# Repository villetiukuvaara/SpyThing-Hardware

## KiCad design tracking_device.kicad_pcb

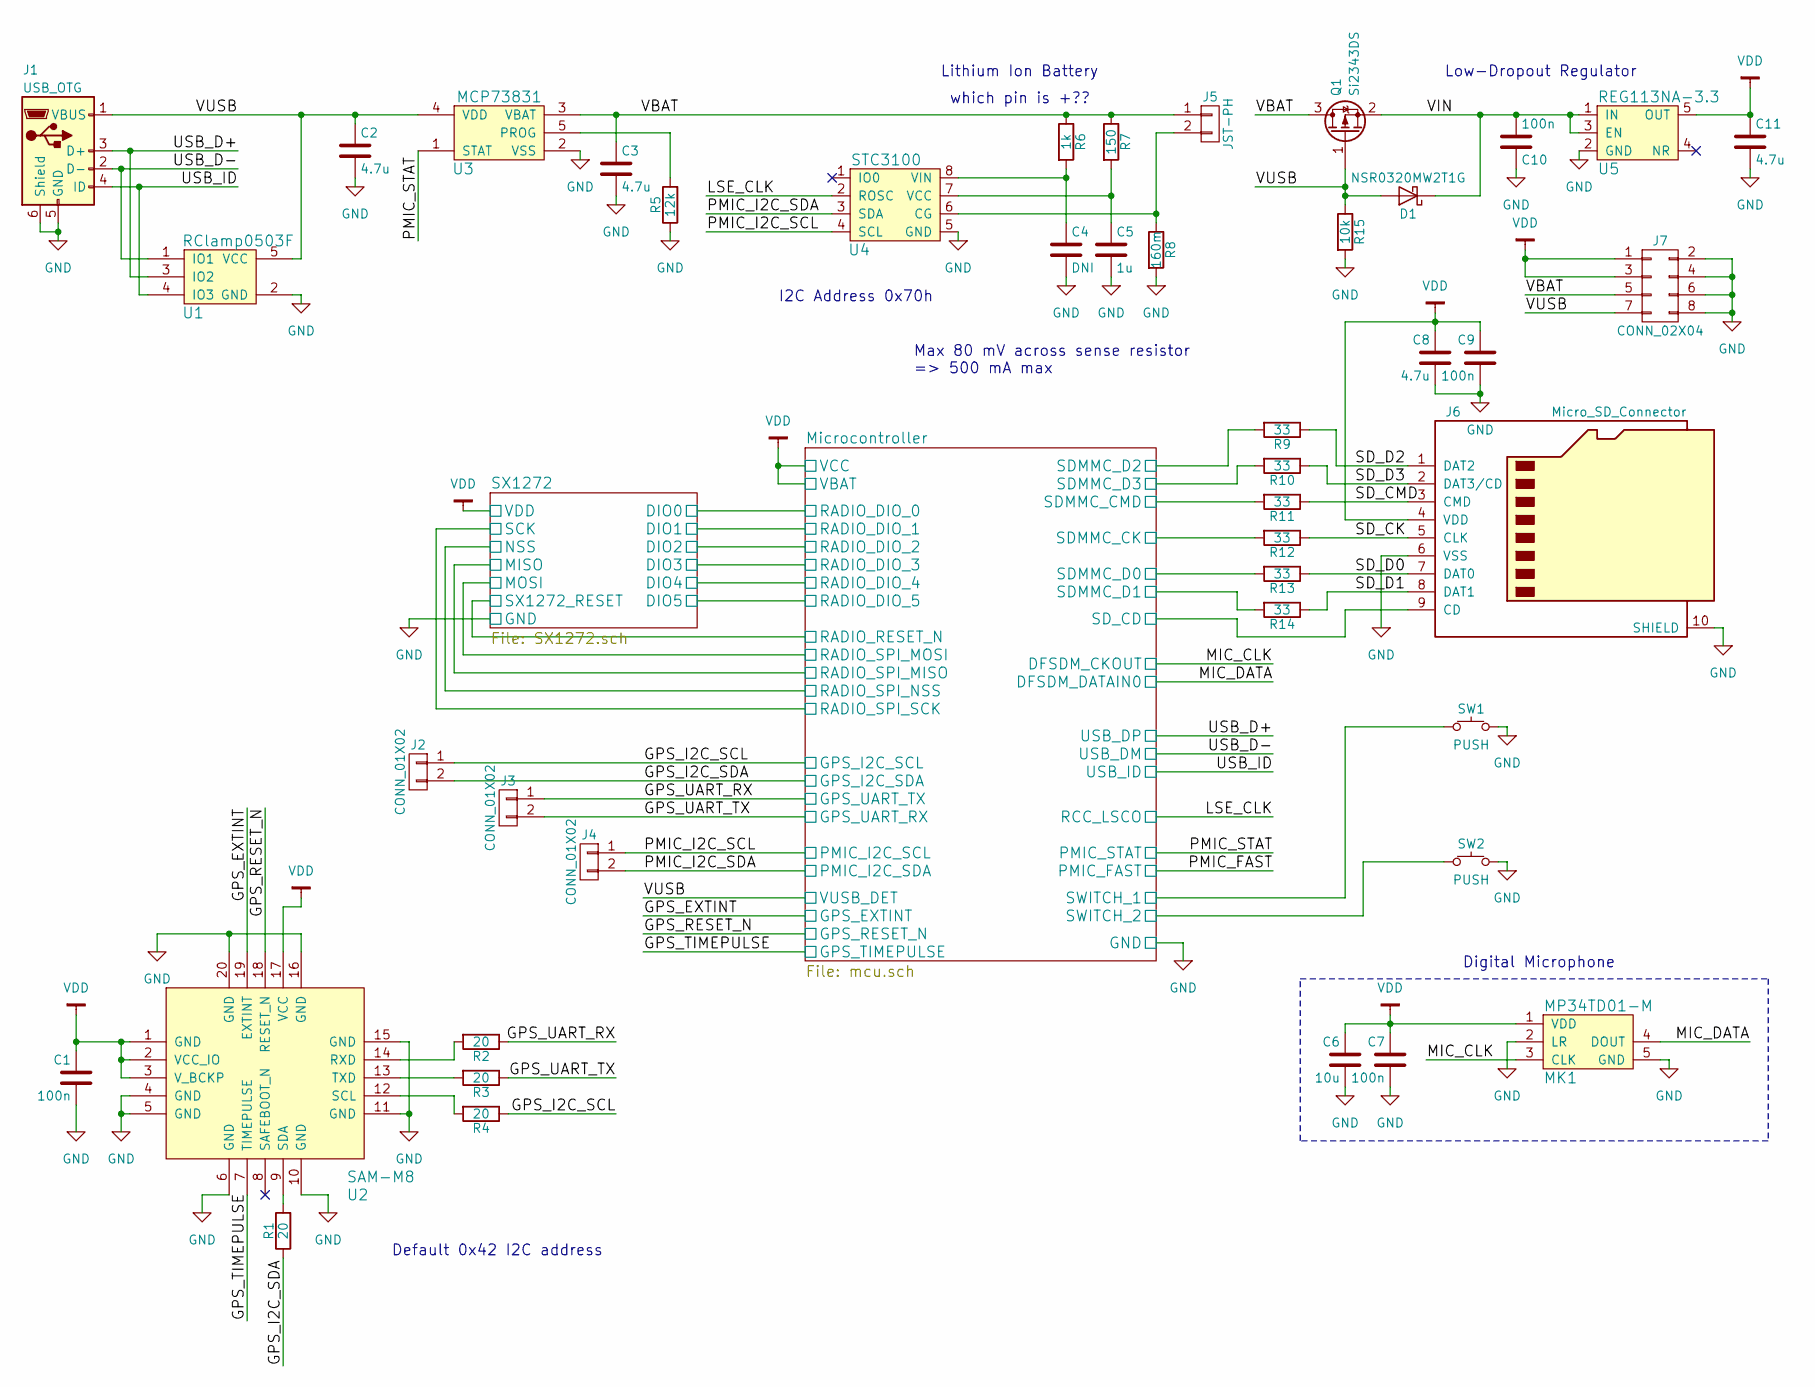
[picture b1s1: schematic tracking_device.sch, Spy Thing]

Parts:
C1, C7, C9, C10: 100n; C_0805_HandSoldering
C2, C3, C8, C11: 4.7u; C_0805_HandSoldering
C4: DNI; C_0805_HandSoldering
C5: 1u; C_0805_HandSoldering
C6: 10u; C_0805_HandSoldering
D1: NSR0320MW2T1G; D_SOD-323_HandSoldering
J1: USB_OTG; FCI_10118192-0001LF
J2, J3, J4: CONN_01X02; Pin_Header_Straight_2x01_Pitch2.54mm
J5: JST-PH; PH-2AWD
J6: Micro_SD_Connector; SD_Card_Connector_Ebay
J7: CONN_02X04; HEADER_M_2.54MM_2R8P_ST_AU_PTH
MK1: MP34TD01-M; MIC_3x4
Q1: Si2343DS; SOT-23_Handsoldering
R1, R2, R3, R4: 20; R_0805_HandSoldering
R5: 12k; R_0805_HandSoldering
R6: 1k; R_0805_HandSoldering
R7: 150; R_0805_HandSoldering
R8: 160m; R_0805_HandSoldering
R9, R10, R11, R12, R13, R14: 33; R_0805_HandSoldering
R15: 10k; R_0805_HandSoldering
SW1, SW2: PUSH; SW_3.1x3.1
U1: RClamp0503F; SOT-353_SC-70-5_Handsoldering
U2: SAM-M8
U3: MCP73831; SOT-23-5
U4: STC3100; DFN-8-1EP_3x3mm_Pitch0.5mm
U5: REG113NA-3.3; SOT-23-5_HandSoldering

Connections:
/GPS_EXTINT: U2.19 (EXTINT); also elsewhere on the board
/GPS_I2C_SCL: J2.1, R4.1; also elsewhere on the board
/GPS_I2C_SDA: J2.2, R1.1; also elsewhere on the board
/GPS_RESET_N: U2.18 (RESET_N); also elsewhere on the board
/GPS_TIMEPULSE: U2.7 (TIMEPULSE); also elsewhere on the board
/GPS_UART_RX: J3.1, R2.1; also elsewhere on the board
/GPS_UART_TX: J3.2, R3.1; also elsewhere on the board
/LSE_CLK: U4.2 (ROSC); also elsewhere on the board
/MIC_CLK: MK1.3 (CLK); also elsewhere on the board
/MIC_DATA: MK1.4 (DOUT); also elsewhere on the board
/Microcontroller/SDMMC_CK: R12.2; also elsewhere on the board
/Microcontroller/SDMMC_CMD: R11.2; also elsewhere on the board
/Microcontroller/SDMMC_D0: R13.2; also elsewhere on the board
/Microcontroller/SDMMC_D1: R14.2; also elsewhere on the board
/Microcontroller/SDMMC_D2: R9.2; also elsewhere on the board
/Microcontroller/SDMMC_D3: R10.2; also elsewhere on the board
/Microcontroller/SD_CD: J6.9 (CD); also elsewhere on the board
/Microcontroller/SWITCH_1: SW1.1; also elsewhere on the board
/Microcontroller/SWITCH_2: SW2.1; also elsewhere on the board
/PMIC_I2C_SCL: J4.1, U4.4 (SCL); also elsewhere on the board
/PMIC_I2C_SDA: J4.2, U4.3 (SDA); also elsewhere on the board
/PMIC_STAT: U3.1 (STAT); also elsewhere on the board
/SD_CK: J6.5 (CLK), R12.1
/SD_CMD: J6.3 (CMD), R11.1
/SD_D0: J6.7 (DAT0), R13.1
/SD_D1: J6.8 (DAT1), R14.1
/SD_D2: J6.1 (DAT2), R9.1
/SD_D3: J6.2 (DAT3/CD), R10.1
/USB_D+: J1.3 (D+), U1.3 (IO2); also elsewhere on the board
/USB_D-: J1.2 (D-), U1.1 (IO1); also elsewhere on the board
/USB_ID: J1.4 (ID), U1.4 (IO3); also elsewhere on the board
/VBAT: C3.1, J5.1, J7.5, Q1.3 (D), R6.1, R7.1, U3.3 (VBAT)
/VIN: C10.2, D1.1 (K), Q1.2 (S), U5.1 (IN), U5.3 (EN)
/VUSB: C2.1, D1.2 (A), J1.1 (VBUS), J7.7, Q1.1 (G), R15.1, U1.5 (VCC), U3.4 (VDD); also elsewhere on the board
GND: C1.2, C2.2, C3.2, C4.2, C5.2, C6.2, C7.2, C8.2, C9.2, C10.1, C11.2, J1.5 (GND), J1.6 (Shield), J6.6 (VSS), J6.10 (SHIELD), J7.2, J7.4, J7.6, J7.8, MK1.2 (LR), MK1.5 (GND), R5.1, R8.2, R15.2, SW1.2, SW2.2, U1.2 (GND), U2.4 (GND), U2.5 (GND), U2.6 (GND), U2.10 (GND), U2.11 (GND), U2.15 (GND), U2.16 (GND), U2.20 (GND), U3.2 (VSS), U4.5 (GND), U5.2 (GND); also elsewhere on the board
unnamed: C4.1, R6.2, U4.8 (VIN)
unnamed: C5.1, R7.2, U4.7 (VCC)
unnamed: J5.2, R8.1, U4.6 (CG)
unnamed: R1.2, U2.9 (SDA)
unnamed: R2.2, U2.14 (RXD)
unnamed: R3.2, U2.13 (TXD)
unnamed: R4.2, U2.12 (SCL)
unnamed: R5.2, U3.5 (PROG)
VDD: C1.1, C6.1, C7.1, C8.1, C9.1, C11.1, J6.4 (VDD), J7.1, J7.3, MK1.1 (VDD), U2.1 (GND), U2.2 (VCC_IO), U2.3 (V_BCKP), U2.17 (VCC), U5.5 (OUT); also elsewhere on the board

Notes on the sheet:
Lithium Ion Battery
Low-Dropout Regulator
Max 80 mV across sense resistor => 500 mA max
Digital Microphone
I2C Address 0x70h
Default 0x42 I2C address
which pin is +??

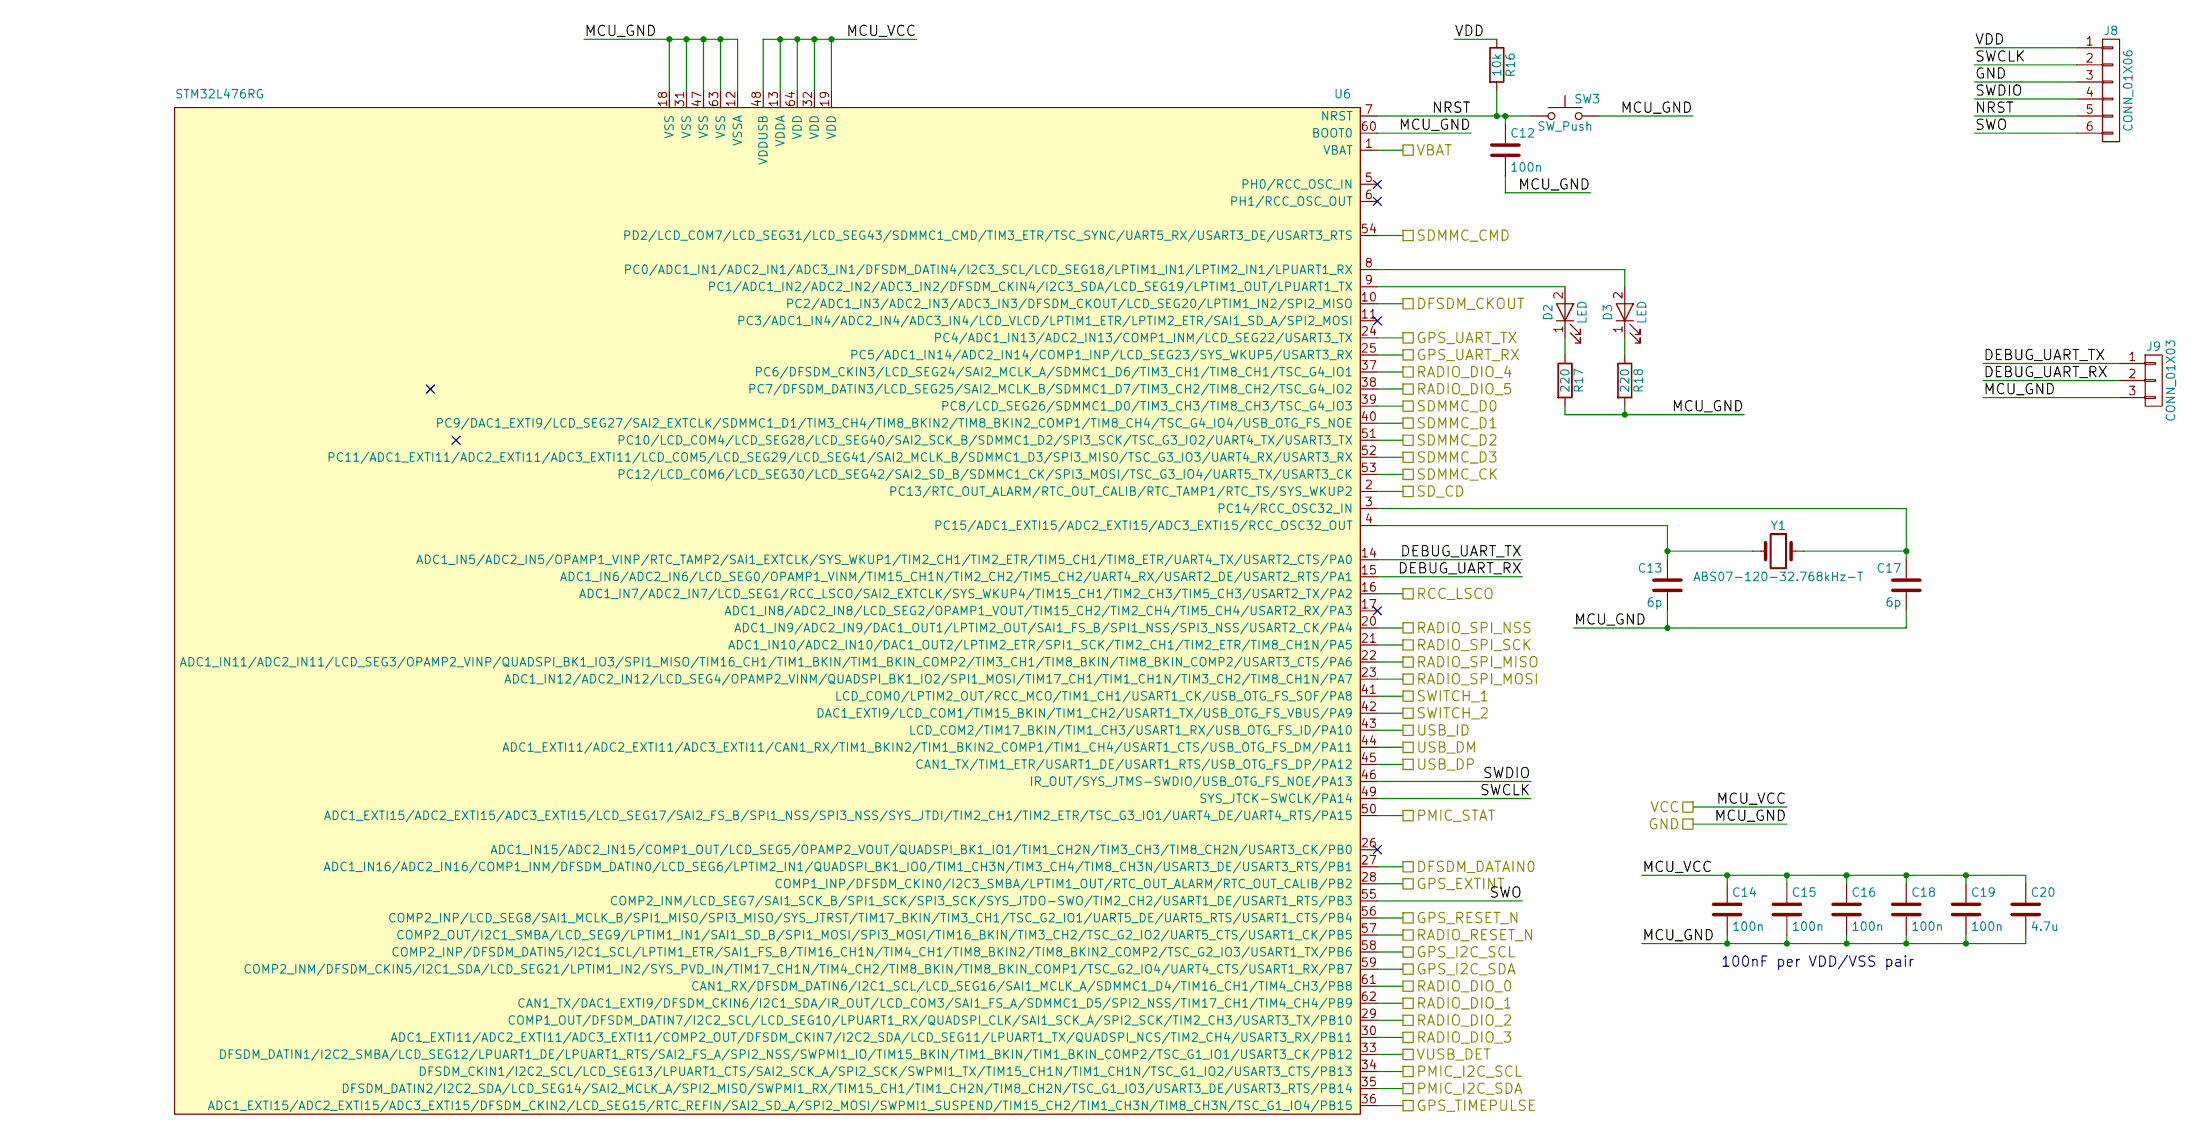
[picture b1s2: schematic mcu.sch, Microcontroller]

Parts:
C12, C14, C15, C16, C18, C19: 100n; C_0805_HandSoldering
C13, C17: 6p; C_0805_HandSoldering
C20: 4.7u; C_0805_HandSoldering
D2, D3: LED; LED_0805_HandSoldering
J8: CONN_01X06; Pin_Header_Straight_1x06_Pitch2.54mm
J9: CONN_01X03; Pin_Header_Straight_1x03_Pitch2.54mm
R16: 10k; R_0805_HandSoldering
R17, R18: 220; R_0805_HandSoldering
SW3: SW_Push; SW_PUSH_6mm
U6: STM32L476RG; LQFP-64_10x10mm_Pitch0.5mm
Y1: ABS07-120-32.768kHz-T; Crystal_SMD_MicroCrystal_CC7V-T1A-2pin_3.2x1.5mm_HandSolder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

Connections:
/GPS_EXTINT: U6.28 (COMP1_INP/DFSDM_CKIN0/I2C3_SMBA/LPTIM1_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); also elsewhere on the board
/GPS_I2C_SCL: U6.58 (COMP2_INP/DFSDM_DATIN5/I2C1_SCL/LPTIM1_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); also elsewhere on the board
/GPS_I2C_SDA: U6.59 (COMP2_INM/DFSDM_CKIN5/I2C1_SDA/LCD_SEG2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); also elsewhere on the board
/GPS_RESET_N: U6.56 (COMP2_INP/LCD_SEG8/SAI1_MCLK_B/SPI1_MIS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); also elsewhere on the board
/GPS_TIMEPULSE: U6.36 (ADC1_EXTI15/ADC2_EXTI15/ADC3_EXTI15/DFS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); also elsewhere on the board
/GPS_UART_RX: U6.24 (PC4/ADC1_IN13/ADC2_IN13/COMP1_INM/LCD_S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); also elsewhere on the board
/GPS_UART_TX: U6.25 (PC5/ADC1_IN14/ADC2_IN14/COMP1_INP/LCD_S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); also elsewhere on the board
/LSE_CLK: U6.16 (ADC1_IN7/ADC2_IN7/LCD_SEG1/RCC_LSCO/SAI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); also elsewhere on the board
/MIC_CLK: U6.10 (PC2/ADC1_IN3/ADC2_IN3/ADC3_IN3/DFSDM_CK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); also elsewhere on the board
/MIC_DATA: U6.27 (ADC1_IN16/ADC2_IN16/COMP1_INM/DFSDM_DAT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); also elsewhere on the board
/Microcontroller/DEBUG_UART_RX: J9.2, U6.15 (ADC1_IN6/ADC2_IN6/LCD_SEG0/OPAMP1_VINM/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)
/Microcontroller/DEBUG_UART_TX: J9.1, U6.14 (ADC1_IN5/ADC2_IN5/OPAMP1_VINP/RTC_TAMP2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)
/Microcontroller/NRST: C12.1, J8.5, R16.2, SW3.1, U6.7 (NRST)
/Microcontroller/RADIO_RESET_N: U6.57 (COMP2_OUT/I2C1_SMBA/LCD_SEG9/LPTIM1_IN1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); also elsewhere on the board
/Microcontroller/RADIO_SPI_SCK: U6.21 (ADC1_IN10/ADC2_IN10/DAC1_OUT2/LPTIM2_ET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); also elsewhere on the board
/Microcontroller/SDMMC_CK: U6.53 (PC12/LCD_COM6/LCD_SEG30/LCD_SEG42/SAI2_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); also elsewhere on the board
/Microcontroller/SDMMC_CMD: U6.54 (PD2/LCD_COM7/LCD_SEG31/LCD_SEG43/SDMMC1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); also elsewhere on the board
/Microcontroller/SDMMC_D0: U6.39 (PC8/LCD_SEG26/SDMMC1_D0/TIM3_CH3/TIM8_C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); also elsewhere on the board
/Microcontroller/SDMMC_D1: U6.40 (PC9/DAC1_EXTI9/LCD_SEG27/SAI2_EXTCLK/SD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); also elsewhere on the board
/Microcontroller/SDMMC_D2: U6.51 (PC10/LCD_COM4/LCD_SEG28/LCD_SEG40/SAI2_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); also elsewhere on the board
/Microcontroller/SDMMC_D3: U6.52 (PC11/ADC1_EXTI11/ADC2_EXTI11/ADC3_EXTI1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); also elsewhere on the board
/Microcontroller/SD_CD: U6.2 (PC13/RTC_OUT_ALARM/RTC_OUT_CALIB/RTC_TA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); also elsewhere on the board
/Microcontroller/SWCLK: J8.2, U6.49 (SYS_JTCK-SWCLK/PA14)
/Microcontroller/SWDIO: J8.4, U6.46 (IR_OUT/SYS_JTMS-SWDIO/USB_OTG_FS_NOE/PA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)
/Microcontroller/SWITCH_1: U6.41 (LCD_COM0/LPTIM2_OUT/RCC_MCO/TIM1_CH1/US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); also elsewhere on the board
/Microcontroller/SWITCH_2: U6.42 (DAC1_EXTI9/LCD_COM1/TIM15_BKIN/TIM1_CH2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); also elsewhere on the board
/Microcontroller/SWO: J8.6, U6.55 (COMP2_INM/LCD_SEG7/SAI1_SCK_B/SPI1_SCK/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)
/PMIC_I2C_SCL: U6.34 (DFSDM_CKIN1/I2C2_SCL/LCD_SEG13/LPUART1_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); also elsewhere on the board
/PMIC_I2C_SDA: U6.35 (DFSDM_DATIN2/I2C2_SDA/LCD_SEG14/SAI2_MC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); also elsewhere on the board
/PMIC_STAT: U6.50 (ADC1_EXTI15/ADC2_EXTI15/ADC3_EXTI15/LCD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); also elsewhere on the board
/SX1272/DIO0: U6.61 (CAN1_RX/DFSDM_DATIN6/I2C1_SCL/LCD_SEG16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); also elsewhere on the board
/SX1272/DIO1: U6.62 (CAN1_TX/DAC1_EXTI9/DFSDM_CKIN6/I2C1_SDA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); also elsewhere on the board
/SX1272/DIO2: U6.29 (COMP1_OUT/DFSDM_DATIN7/I2C2_SCL/LCD_SEG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); also elsewhere on the board
/SX1272/DIO3: U6.30 (ADC1_EXTI11/ADC2_EXTI11/ADC3_EXTI11/COM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); also elsewhere on the board
/SX1272/DIO4: U6.37 (PC6/DFSDM_CKIN3/LCD_SEG24/SAI2_MCLK_A/S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); also elsewhere on the board
/SX1272/DIO5: U6.38 (PC7/DFSDM_DATIN3/LCD_SEG25/SAI2_MCLK_B/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); also elsewhere on the board
/SX1272/MISO: U6.22 (ADC1_IN11/ADC2_IN11/LCD_SEG3/OPAMP2_VIN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); also elsewhere on the board
/SX1272/MOSI: U6.23 (ADC1_IN12/ADC2_IN12/LCD_SEG4/OPAMP2_VIN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); also elsewhere on the board
/SX1272/NSS: U6.20 (ADC1_IN9/ADC2_IN9/DAC1_OUT1/LPTIM2_OUT/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); also elsewhere on the board
/USB_D+: U6.45 (CAN1_TX/TIM1_ETR/USART1_DE/USART1_RTS/U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); also elsewhere on the board
/USB_D-: U6.44 (ADC1_EXTI11/ADC2_EXTI11/ADC3_EXTI11/CAN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); also elsewhere on the board
/USB_ID: U6.43 (LCD_COM2/TIM17_BKIN/TIM1_CH3/USART1_RX/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); also elsewhere on the board
/VUSB: U6.33 (DFSDM_DATIN1/I2C2_SMBA/LCD_SEG12/LPUART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); also elsewhere on the board
GND: C12.2, C13.2, C14.2, C15.2, C16.2, C17.2, C18.2, C19.2, C20.2, J8.3, J9.3, R17.2, R18.2, SW3.2, U6.12 (VSSA), U6.18 (VSS), U6.31 (VSS), U6.47 (VSS), U6.60 (BOOT0), U6.63 (VSS); also elsewhere on the board
unnamed: C13.1, U6.4 (PC15/ADC1_EXTI15/ADC2_EXTI15/ADC3_EXTI1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), Y1.2
unnamed: C17.1, U6.3 (PC14/RCC_OSC32_IN), Y1.1
unnamed: D2.1 (K), R17.1
unnamed: D2.2 (A), U6.9 (PC1/ADC1_IN2/ADC2_IN2/ADC3_IN2/DFSDM_CK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)
unnamed: D3.1 (K), R18.1
unnamed: D3.2 (A), U6.8 (PC0/ADC1_IN1/ADC2_IN1/ADC3_IN1/DFSDM_DA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)
VDD: C14.1, C15.1, C16.1, C18.1, C19.1, C20.1, J8.1, R16.1, U6.1 (VBAT), U6.13 (VDDA), U6.19 (VDD), U6.32 (VDD), U6.48 (VDDUSB), U6.64 (VDD); also elsewhere on the board

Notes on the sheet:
100nF per VDD/VSS pair

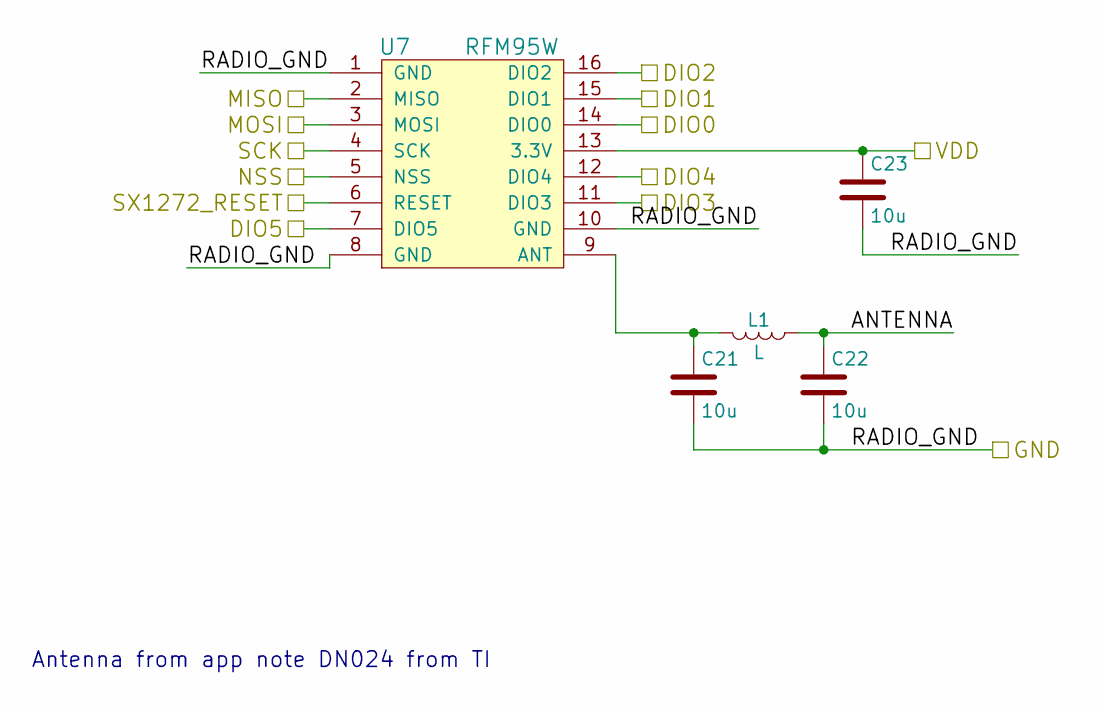
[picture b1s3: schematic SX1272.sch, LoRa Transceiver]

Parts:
C21, C22, C23: 10u; C_0805_HandSoldering
L1: L; L_0805_HandSoldering
U7: RFM95W

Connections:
/Microcontroller/RADIO_RESET_N: U7.6 (RESET); also elsewhere on the board
/Microcontroller/RADIO_SPI_SCK: U7.4 (SCK); also elsewhere on the board
/SX1272/ANTENNA: C22.1, L1.1
/SX1272/DIO0: U7.14 (DIO0); also elsewhere on the board
/SX1272/DIO1: U7.15 (DIO1); also elsewhere on the board
/SX1272/DIO2: U7.16 (DIO2); also elsewhere on the board
/SX1272/DIO3: U7.11 (DIO3); also elsewhere on the board
/SX1272/DIO4: U7.12 (DIO4); also elsewhere on the board
/SX1272/DIO5: U7.7 (DIO5); also elsewhere on the board
/SX1272/MISO: U7.2 (MISO); also elsewhere on the board
/SX1272/MOSI: U7.3 (MOSI); also elsewhere on the board
/SX1272/NSS: U7.5 (NSS); also elsewhere on the board
GND: C21.2, C22.2, C23.2, U7.1 (GND), U7.8 (GND), U7.10 (GND); also elsewhere on the board
unnamed: C21.1, L1.2, U7.9 (ANT)
VDD: C23.1, U7.13 (3.3V); also elsewhere on the board

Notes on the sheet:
Antenna from app note DN024 from TI

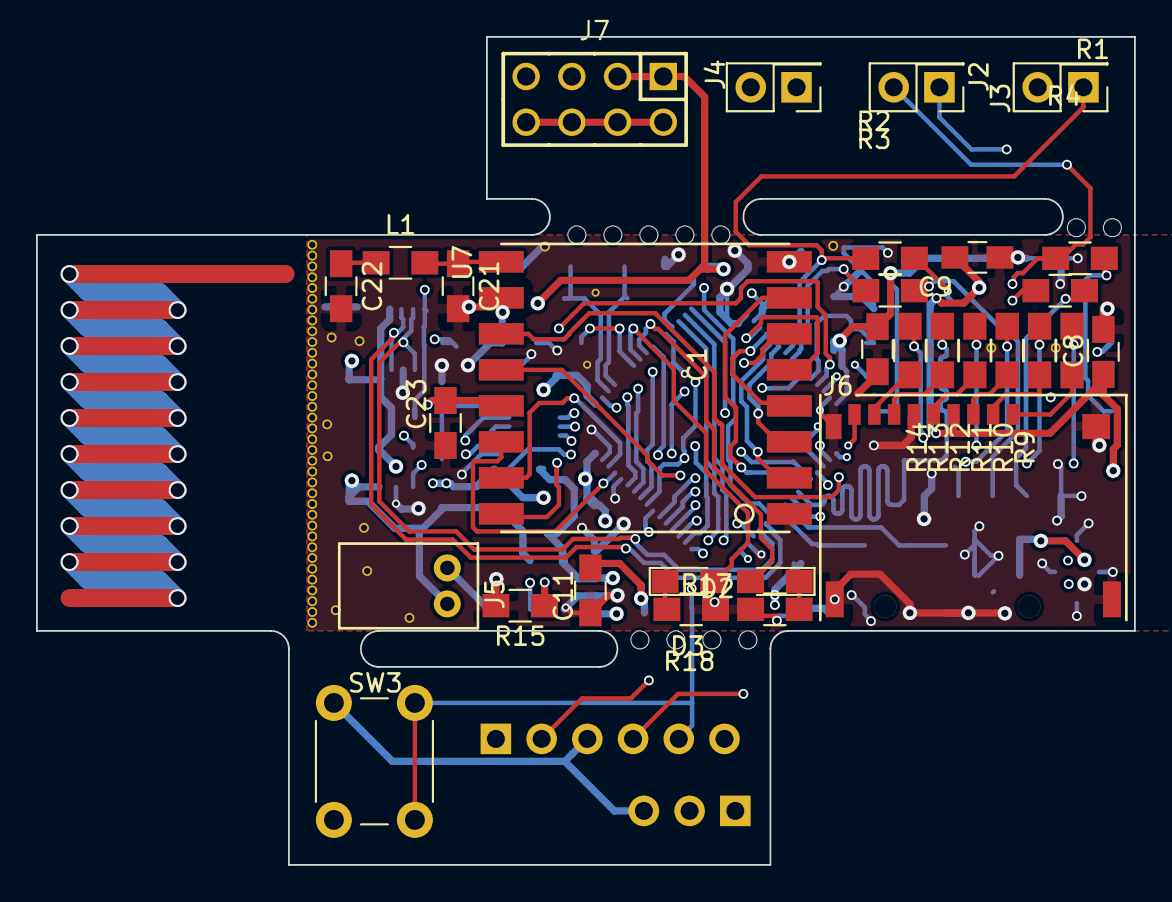
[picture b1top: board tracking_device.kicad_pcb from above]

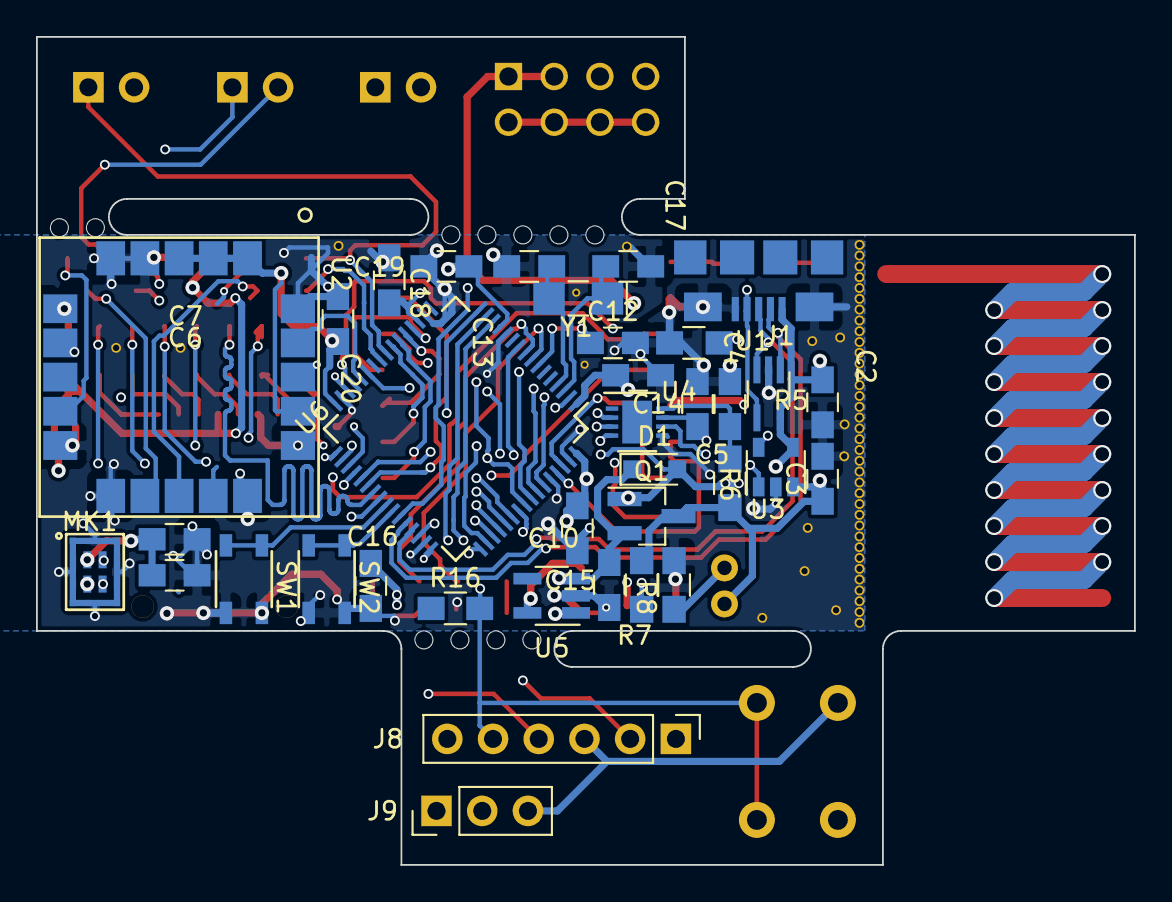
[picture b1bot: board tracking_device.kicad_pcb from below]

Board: 4 copper layers, 61.0 x 46.0 mm, 67 parts (36 on the bottom side), 69 nets.

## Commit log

2017-10-07 Added microphone footprint
2017-10-07 Added U-Blox Max footprint
2017-10-22 Most components arranged on PCB
2017-10-23 Added RFM95W
2017-11-11 Version sent out for fabrication
2017-11-22 Rev 1 sent for fabrication
2017-11-22 Create LICENSE
2018-01-27 Changes before starting rev 2
2018-04-13 Working on rev 3, started board layout
2018-04-26 Rev 3 DRC clean
